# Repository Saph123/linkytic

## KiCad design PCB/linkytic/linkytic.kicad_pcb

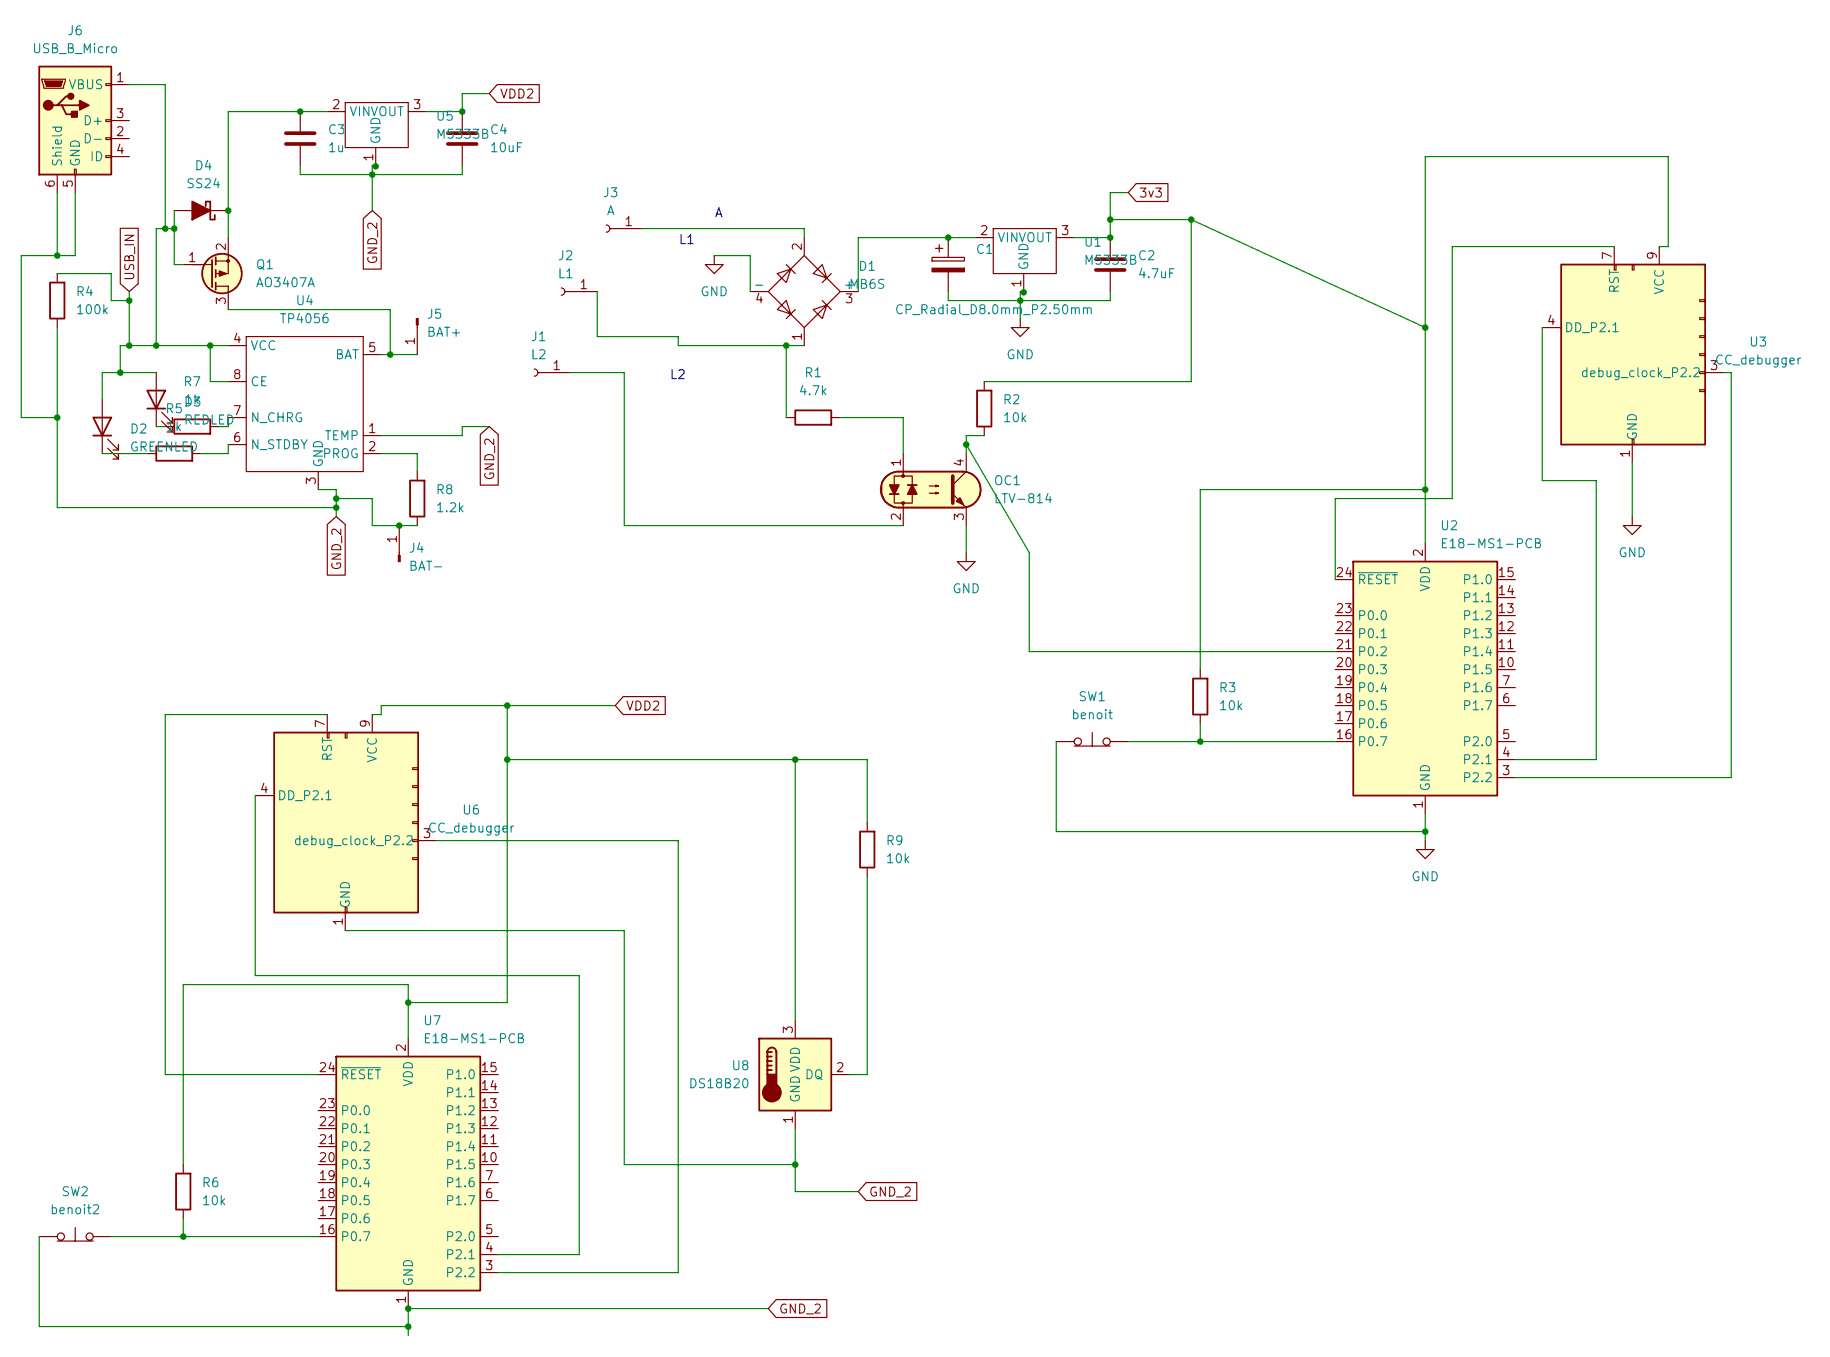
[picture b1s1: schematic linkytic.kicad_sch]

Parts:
C1: CP_Radial_D8.0mm_P2.50mm
C2: 4.7uF; C_0603_1608Metric
C3: 1u; C_0603_1608Metric
C4: 10uF; C_0603_1608Metric
D1: MB6S; TO-269AA
D2: GREENLED; LED_0805_2012Metric_Pad1.15x1.40mm_HandSolder
D3: REDLED
D4: SS24; D_SMB
J1: L2; TestPoint_Loop_D2.54mm_Drill1.5mm_Beaded
J2: L1; TestPoint_Loop_D2.54mm_Drill1.5mm_Beaded
J3: A; TestPoint_Loop_D2.54mm_Drill1.5mm_Beaded
J4: BAT-; PinHeader_1x01_P1.27mm_Vertical
J5: BAT+; PinHeader_1x01_P1.27mm_Vertical
J6: USB_B_Micro; USB_aliexpress
OC1: LTV-814; DIP-4_W7.62mm_LongPads
Q1: AO3407A; SOT-23
R1: 4.7k; R_0603_1608Metric_Pad0.98x0.95mm_HandSolder
R2, R3, R6, R9: 10k; R_0603_1608Metric_Pad0.98x0.95mm_HandSolder
R4: 100k; R_0603_1608Metric_Pad0.98x0.95mm_HandSolder
R5, R7: 1k; R_0603_1608Metric_Pad0.98x0.95mm_HandSolder
R8: 1.2k; R_0603_1608Metric_Pad0.98x0.95mm_HandSolder
SW1: benoit; interrupteur
SW2: benoit2; interrupteur
U1, U5: M5333B; SOT-89-3_Handsoldering
U2, U7: E18-MS1-PCB
U3, U6: CC_debugger; IDC-Header_2x05_P2.54mm_Vertical
U4: TP4056; SOP-8_3.76x4.96mm_P1.27mm
U8: DS18B20; TO-92_Inline

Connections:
3v3: C2.1, R2.2, R3.2, U1.3 (VOUT), U2.2 (VDD), U3.9 (VCC)
GND: C1.2, C2.2, D1.4 (-), OC1.3, SW1.1 (A), U1.1 (GND), U2.1 (GND), U3.1 (GND)
GND_2: C3.2, C4.2, J4.1, J6.5 (GND), J6.6 (Shield), R4.1, R8.1, SW2.1 (A), U4.1 (TEMP), U4.3 (GND), U5.1 (GND), U6.1 (GND), U7.1 (GND), U8.1 (GND); also elsewhere on the board
unnamed: C1.1, D1.3 (+), U1.2 (VIN)
unnamed: D1.1, J2.1, R1.1
unnamed: D1.2, J3.1
unnamed: D2.1 (K), R5.1
unnamed: D3.1 (K), R7.1
unnamed: C3.1, D4.1 (K), Q1.2 (S), U5.2 (VIN)
unnamed: J1.1, OC1.2
unnamed: J5.1, Q1.3 (D), U4.5 (BAT)
unnamed: OC1.1, R1.2
unnamed: OC1.4, R2.1, U2.21 (P0.2)
unnamed: R3.1, SW1.2 (B), U2.16 (P0.7)
unnamed: R5.2, U4.6 (N_STDBY)
unnamed: R6.1, SW2.2 (B), U7.16 (P0.7)
unnamed: R7.2, U4.7 (N_CHRG)
unnamed: R8.2, U4.2 (PROG)
unnamed: R9.1, U8.2 (DQ)
unnamed: U2.3 (P2.2), U3.3 (debug_clock_P2.2)
unnamed: U2.4 (P2.1), U3.4 (DD_P2.1)
unnamed: U2.24 (~RESET), U3.7 (RST)
unnamed: U6.3 (debug_clock_P2.2), U7.3 (P2.2)
unnamed: U6.4 (DD_P2.1), U7.4 (P2.1)
unnamed: U6.7 (RST), U7.24 (~RESET)
USB_IN: D2.2 (A), D3.2 (A), D4.2 (A), J6.1 (VBUS), Q1.1 (G), R4.2, U4.4 (VCC), U4.8 (CE)
VDD2: C4.1, R6.2, R9.2, U5.3 (VOUT), U6.9 (VCC), U7.2 (VDD), U8.3 (VDD)

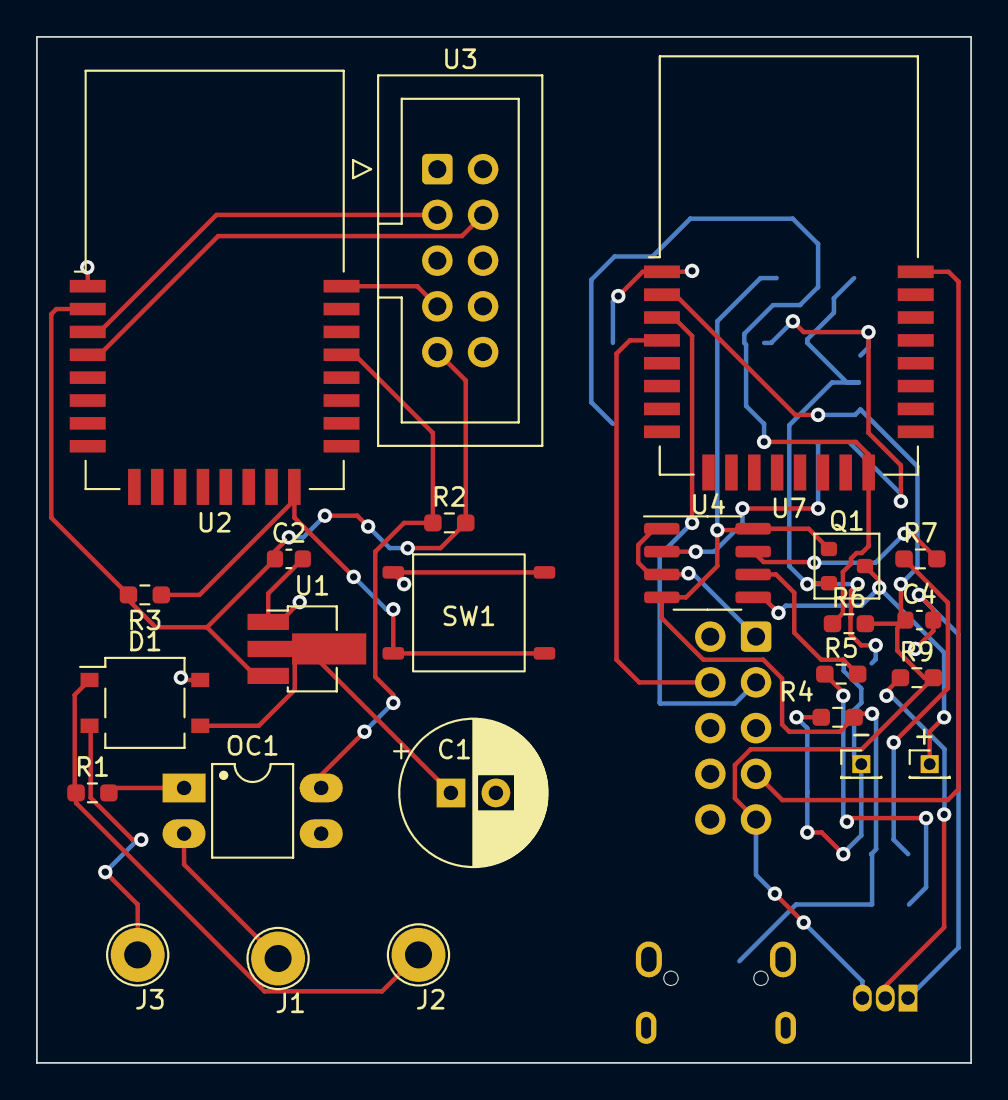
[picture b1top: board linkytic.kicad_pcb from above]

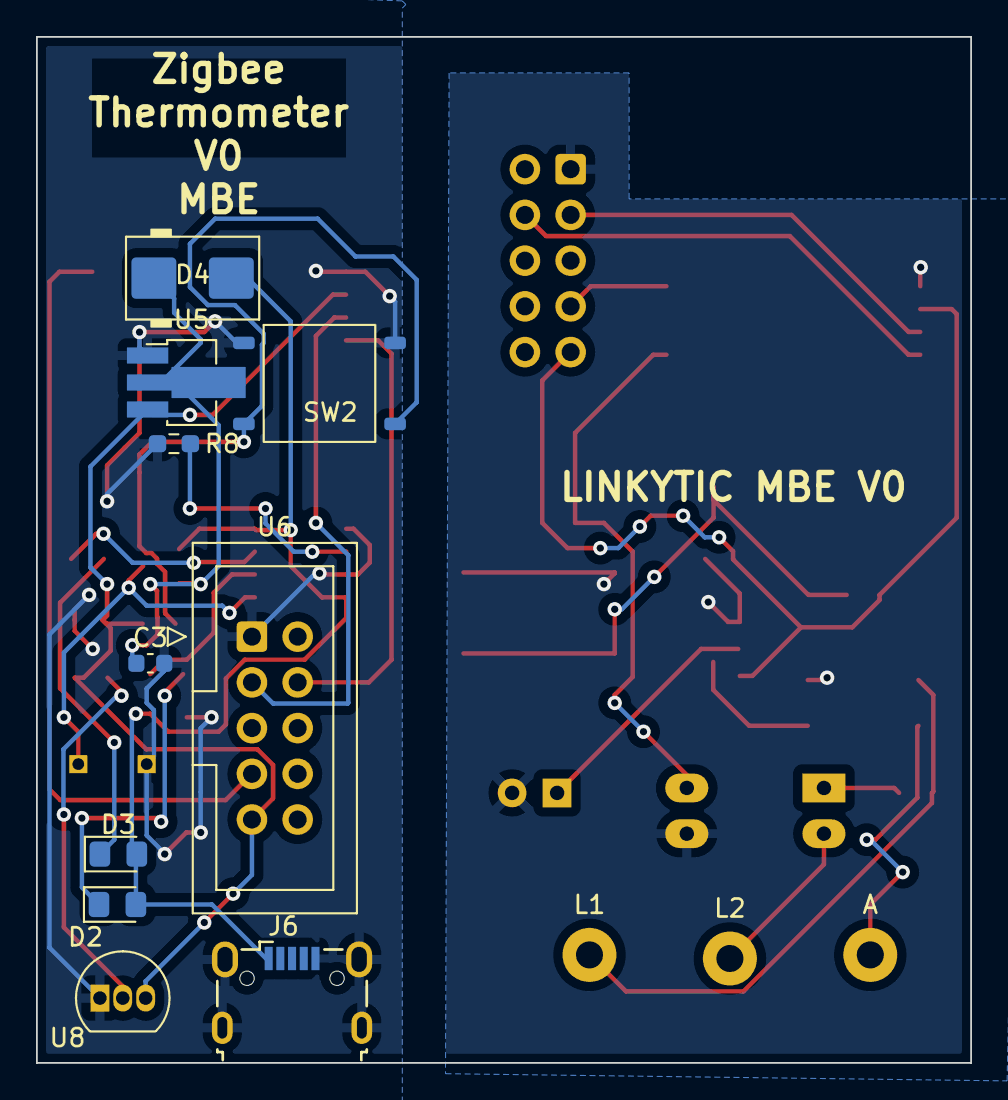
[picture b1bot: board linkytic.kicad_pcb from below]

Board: 2 copper layers, 51.9 x 57.0 mm, 35 parts (10 on the bottom side), 27 nets.

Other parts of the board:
-: BAT-; PinHeader_1x01_P1.27mm_Vertical

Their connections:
GND_2: -.1; also elsewhere on the board

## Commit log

2022-12-06 first version of board, missing antenna and more
2022-12-26 Update with thermometre on same board
2022-12-26 first version, that will notwork :/
2022-12-26 update with A/L1 reversedé
2022-12-29 save before usb adding, last modif
2022-12-30 Update final version V0
2022-12-30 Forgot to save before, this is V0
